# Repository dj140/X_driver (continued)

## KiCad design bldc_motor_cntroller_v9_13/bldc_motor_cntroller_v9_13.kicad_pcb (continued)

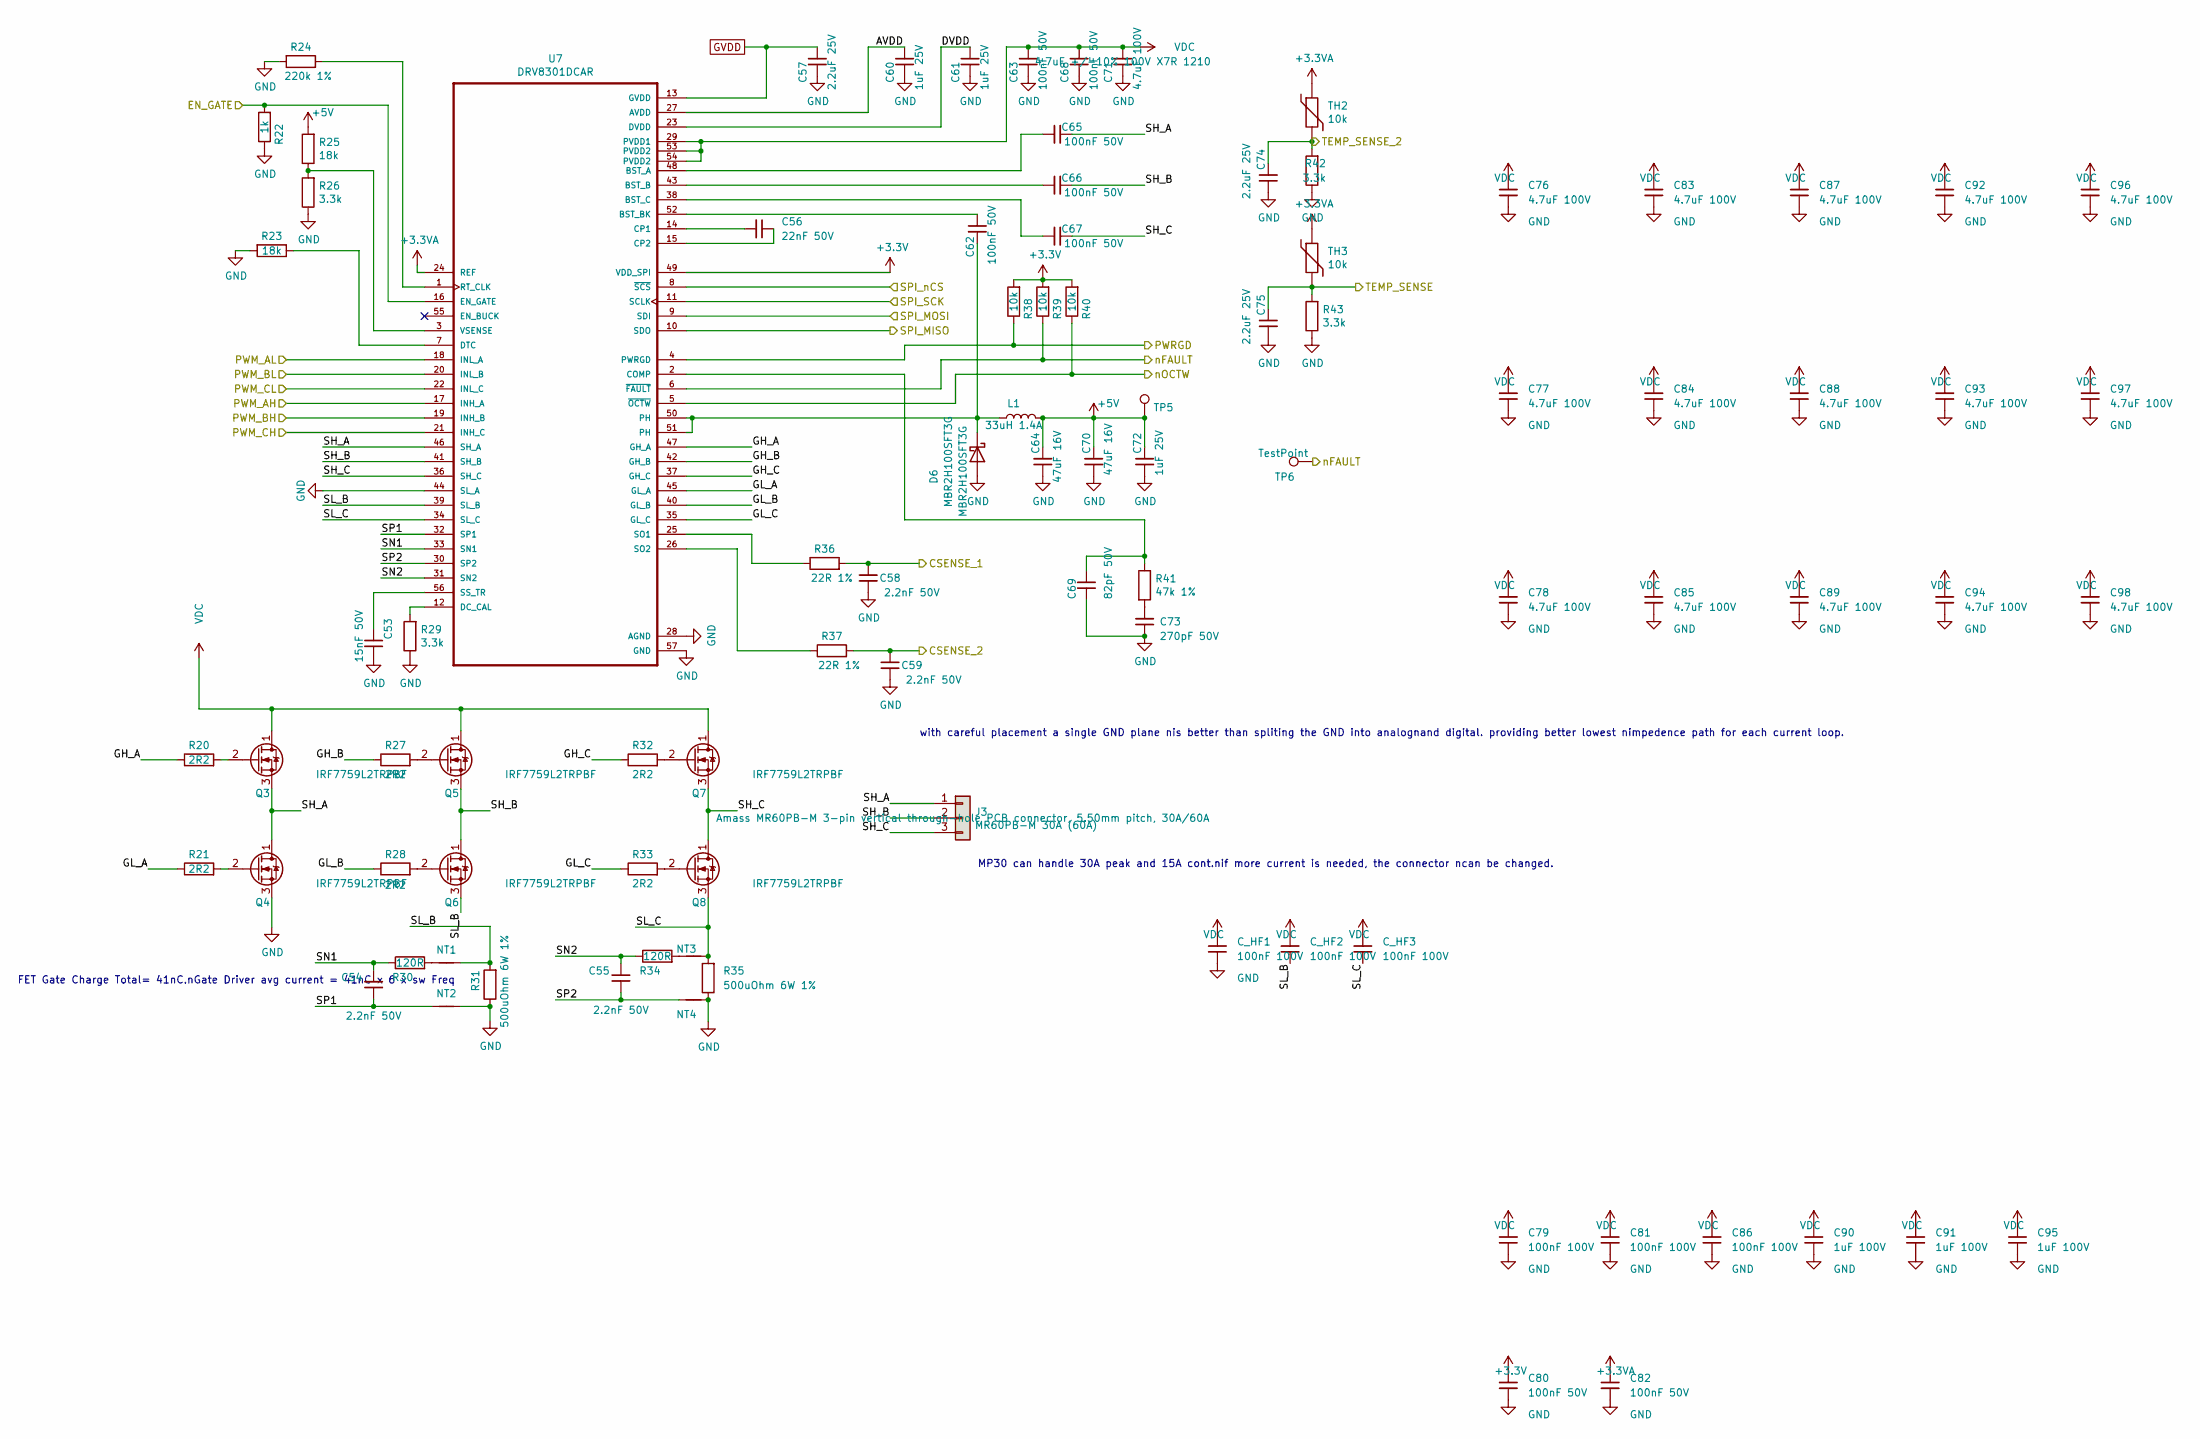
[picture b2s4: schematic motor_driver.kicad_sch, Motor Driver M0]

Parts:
C53: 15nF 50V; C_0402_1005Metric; MPN GCM155R71E153JA55D
C54, C55, C58, C59: 2.2nF 50V; C_0402_1005Metric; MPN C0402C222J3GEC7411; LCSC Part # C1531
C56: 22nF 50V; C_0402_1005Metric; MPN C0402C223K5REC7411; LCSC Part # C1532
C57, C74, C75: 2.2uF 25V; C_0402_1005Metric; MPN GRM155C81E225KE11D; LCSC Part # C12530
C60, C61, C72: 1uF 25V; C_0402_1005Metric; MPN GMK105CC6105MV-F; LCSC Part # C52923
C62, C65, C66, C67: 100nF 50V; C_0402_1005Metric; MPN GCM155L8EH104KE07D
C63, C68: 100nF 50V; C_0402_1005Metric; MPN GRM155R62A104KE14D
C64, C70: 47uF 16V; C_1206_3216Metric; MPN GRM32EC81C476KE15L; LCSC Part # C96123
C69: 82pF 50V; C_0402_1005Metric; MPN VJ0402A820JXACW1BC
C71: 4.7uF 100V; C_1210_3225Metric; MPN GRM32ER72A475KE14L; LCSC Part # C89632
C73: 270pF 50V; C_0402_1005Metric; MPN GRM1555C1H271FA01D
C76, C77, C78, C83, C84, C85, C87, C88, C89, C92, C93, C94, C96, C97, C98: 4.7uF 100V; C_1210_3225Metric; MPN GRM32ER72A475KE14L; LCSC C162515
C79, C81, C86: 100nF 100V; C_0603_1608Metric; MPN GCM188R72A104KA64D; LCSC C15725
C80, C82: 100nF 50V; C_0402_1005Metric; MPN CC0402KRX7R9BB104; LCSC C131394
C90, C91, C95: 1uF 100V; C_0805_2012Metric; MPN 0805B105K101NT; LCSC C396883
C_HF1, C_HF2, C_HF3: 100nF 100V; C_0603_1608Metric; MPN GCM188R72A104KA64D
D6: MBR2H100SFT3G; D_SOD-123F; MPN MBR2H100SFT3G
J3: MR60PB-M 30A (60A); AMASS_MR60PB-M_1x03_P5.50mm_Vertical; MPN MR60PB-M
L1: 33uH 1.4A; L_Taiyo-Yuden_NR-60xx; MPN NR6045T330M
NT1, NT2, NT3, NT4: Net-Tie_2; NetTie-2_SMD_Pad0.5mm
Q3, Q4, Q5, Q6, Q7, Q8: IRF7759L2TRPBF; DirectFET_L8; MPN IRF7759L2TRPBF; LCSC C520641
R20, R21, R27, R28, R32, R33: 2R2; R_0402_1005Metric; MPN CRCW04022R20FKEDC
R22: 1k; R_0402_1005Metric; MPN ERJ-2RKF1001X; LCSC Part # C11702
R23, R25: 18k; R_0402_1005Metric; MPN CRCW040218K0FKED; LCSC Part # C25762
R24: 220k 1%; R_0402_1005Metric; MPN CRCW0402220KFKEDC; LCSC Part # C25767
R26, R29, R42, R43: 3.3k; R_0402_1005Metric; MPN CRCW04023K30FKEDC; LCSC Part # C25890
R30, R34: 120R; R_0402_1005Metric; MPN ERJ-2RKF1200X; LCSC Part # C25079
R31, R35: 500uOhm 6W 1%; R_2512_6332Metric; MPN CSS2H-2512R-L500F
R36, R37: 22R 1%; R_0402_1005Metric; MPN CRCW040222R0FKEDC; LCSC Part # C25092
R38, R39, R40: 10k; R_0402_1005Metric; MPN CRCW040210K0FKEDC; LCSC Part # C25744
R41: 47k 1%; R_0402_1005Metric; MPN CRGP0402F47K; LCSC Part # C25792
TH2, TH3: 10k; R_0402_1005Metric; MPN CRCW040210K0FKEDC
TP5, TP6: TestPoint; TestPoint_Pad_D1.0mm
U7: DRV8301DCAR; DRV8301DCA_v9; MPN DRV8301DCAR

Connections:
+3.3V: C80.1, R38.2, R39.2, R40.2, U7.49 (VDD_SPI); also elsewhere on the board
+3.3VA: C82.1, TH2.1, TH3.1, U7.24 (REF); also elsewhere on the board
+5V: C64.1, C70.1, C72.1, L1.2, R25.2, TP5.1; also elsewhere on the board
/Microcontroller Interface/EN_GATE: R22.2, U7.16 (EN_GATE); also elsewhere on the board
/Microcontroller Interface/M0_AH: U7.17 (INH_A); also elsewhere on the board
/Microcontroller Interface/M0_AL: U7.18 (INL_A); also elsewhere on the board
/Microcontroller Interface/M0_BH: U7.19 (INH_B); also elsewhere on the board
/Microcontroller Interface/M0_BL: U7.20 (INL_B); also elsewhere on the board
/Microcontroller Interface/M0_CH: U7.21 (INH_C); also elsewhere on the board
/Microcontroller Interface/M0_CL: U7.22 (INL_C); also elsewhere on the board
/Microcontroller Interface/M0_SO1: C58.2, R36.2; also elsewhere on the board
/Microcontroller Interface/M0_SO2: C59.2, R37.2; also elsewhere on the board
/Microcontroller Interface/M0_TEMP: C75.1, R43.2, TH3.2; also elsewhere on the board
/Microcontroller Interface/SPI_M0_nCS: U7.8 (~SCS); also elsewhere on the board
/Microcontroller Interface/SPI_MISO: U7.10 (SDO); also elsewhere on the board
/Microcontroller Interface/SPI_MOSI: U7.9 (SDI); also elsewhere on the board
/Microcontroller Interface/SPI_SCK: U7.11 (SCLK); also elsewhere on the board
/Microcontroller Interface/nFAULT: R39.1, TP6.1, U7.6 (~FAULT); also elsewhere on the board
/Motor Driver/AVDD: C60.1, U7.27 (AVDD)
/Motor Driver/DVDD: C61.1, U7.23 (DVDD)
/Motor Driver/GH_A: R20.1, U7.47 (GH_A)
/Motor Driver/GH_B: R27.1, U7.42 (GH_B)
/Motor Driver/GH_C: R32.1, U7.37 (GH_C)
/Motor Driver/GL_A: R21.1, U7.45 (GL_A)
/Motor Driver/GL_B: R28.1, U7.40 (GL_B)
/Motor Driver/GL_C: R33.1, U7.35 (GL_C)
/Motor Driver/PWRGD: R38.1, U7.4 (PWRGD)
/Motor Driver/SH_A: C65.1, J3.1, Q3.3 (S), Q4.1 (D), U7.46 (SH_A)
/Motor Driver/SH_B: C66.1, J3.2, Q5.3 (S), Q6.1 (D), U7.41 (SH_B)
/Motor Driver/SH_C: C67.1, J3.3, Q7.3 (S), Q8.1 (D), U7.36 (SH_C)
/Motor Driver/SL_B: C_HF2.2, NT1.2, Q6.3 (S), R31.2, U7.39 (SL_B)
/Motor Driver/SL_C: C_HF3.2, NT3.2, Q8.3 (S), R35.2, U7.34 (SL_C)
/Motor Driver/SN1: C54.2, R30.1, U7.33 (SN1)
/Motor Driver/SN2: C55.2, R34.1, U7.31 (SN2)
/Motor Driver/SP1: C54.1, NT2.1, U7.32 (SP1)
/Motor Driver/SP2: C55.1, NT4.1, U7.30 (SP2)
/Motor Driver/TEMP_SENSE_2: C74.1, R42.2, TH2.2
/Motor Driver/nOCTW: R40.1, U7.5 (~OCTW)
GND: C53.1, C57.2, C58.1, C59.1, C60.2, C61.2, C63.2, C64.2, C68.2, C69.2, C70.2, C71.2, C72.2, C73.2, C74.2, C75.2, C76.2, C77.2, C78.2, C79.2, C80.2, C81.2, C82.2, C83.2, C84.2, C85.2, C86.2, C87.2, C88.2, C89.2, C90.2, C91.2, C92.2, C93.2, C94.2, C95.2, C96.2, C97.2, C98.2, C_HF1.2, D6.2 (A), NT2.2, NT4.2, Q4.3 (S), R22.1, R23.2, R24.2, R26.1, R29.1, R31.1, R35.1, R42.1, R43.1, U7.28 (AGND), U7.44 (SL_A), U7.57 (GND); also elsewhere on the board
GVDD: C57.1, U7.13 (GVDD); also elsewhere on the board
unnamed: C73.1, R41.2
unnamed: C62.1, D6.1 (K), L1.1, U7.50 (PH), U7.51 (PH)
unnamed: NT1.1, R30.2
unnamed: NT3.1, R34.2
unnamed: Q3.2 (G), R20.2
unnamed: Q4.2 (G), R21.2
unnamed: Q5.2 (G), R27.2
unnamed: Q6.2 (G), R28.2
unnamed: Q7.2 (G), R32.2
unnamed: Q8.2 (G), R33.2
unnamed: C65.2, U7.48 (BST_A)
unnamed: C66.2, U7.43 (BST_B)
unnamed: C62.2, U7.52 (BST_BK)
unnamed: C67.2, U7.38 (BST_C)
unnamed: C69.1, R41.1, U7.2 (COMP)
unnamed: C56.1, U7.14 (CP1)
unnamed: C56.2, U7.15 (CP2)
unnamed: R29.2, U7.12 (DC_CAL)
unnamed: R23.1, U7.7 (DTC)
unnamed: R24.1, U7.1 (RT_CLK)
unnamed: R36.1, U7.25 (SO1)
unnamed: R37.1, U7.26 (SO2)
unnamed: C53.2, U7.56 (SS_TR)
unnamed: R25.1, R26.2, U7.3 (VSENSE)
VDC: C63.1, C68.1, C71.1, C76.1, C77.1, C78.1, C79.1, C81.1, C83.1, C84.1, C85.1, C86.1, C87.1, C88.1, C89.1, C90.1, C91.1, C92.1, C93.1, C94.1, C95.1, C96.1, C97.1, C98.1, C_HF1.1, C_HF2.1, C_HF3.1, Q3.1 (D), Q5.1 (D), Q7.1 (D), U7.29 (PVDD1), U7.53 (PVDD2), U7.54 (PVDD2); also elsewhere on the board

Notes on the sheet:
MP30 can handle 30A peak and 15A cont.nif more current is needed, the connector ncan be changed.
FET Gate Charge Total= 41nC.nGate Driver avg current = 41nC x 6 x sw Freq
with careful placement a single GND plane nis better than spliting the GND into analognand digital. providing better lowest nimpedence path for each current loop.

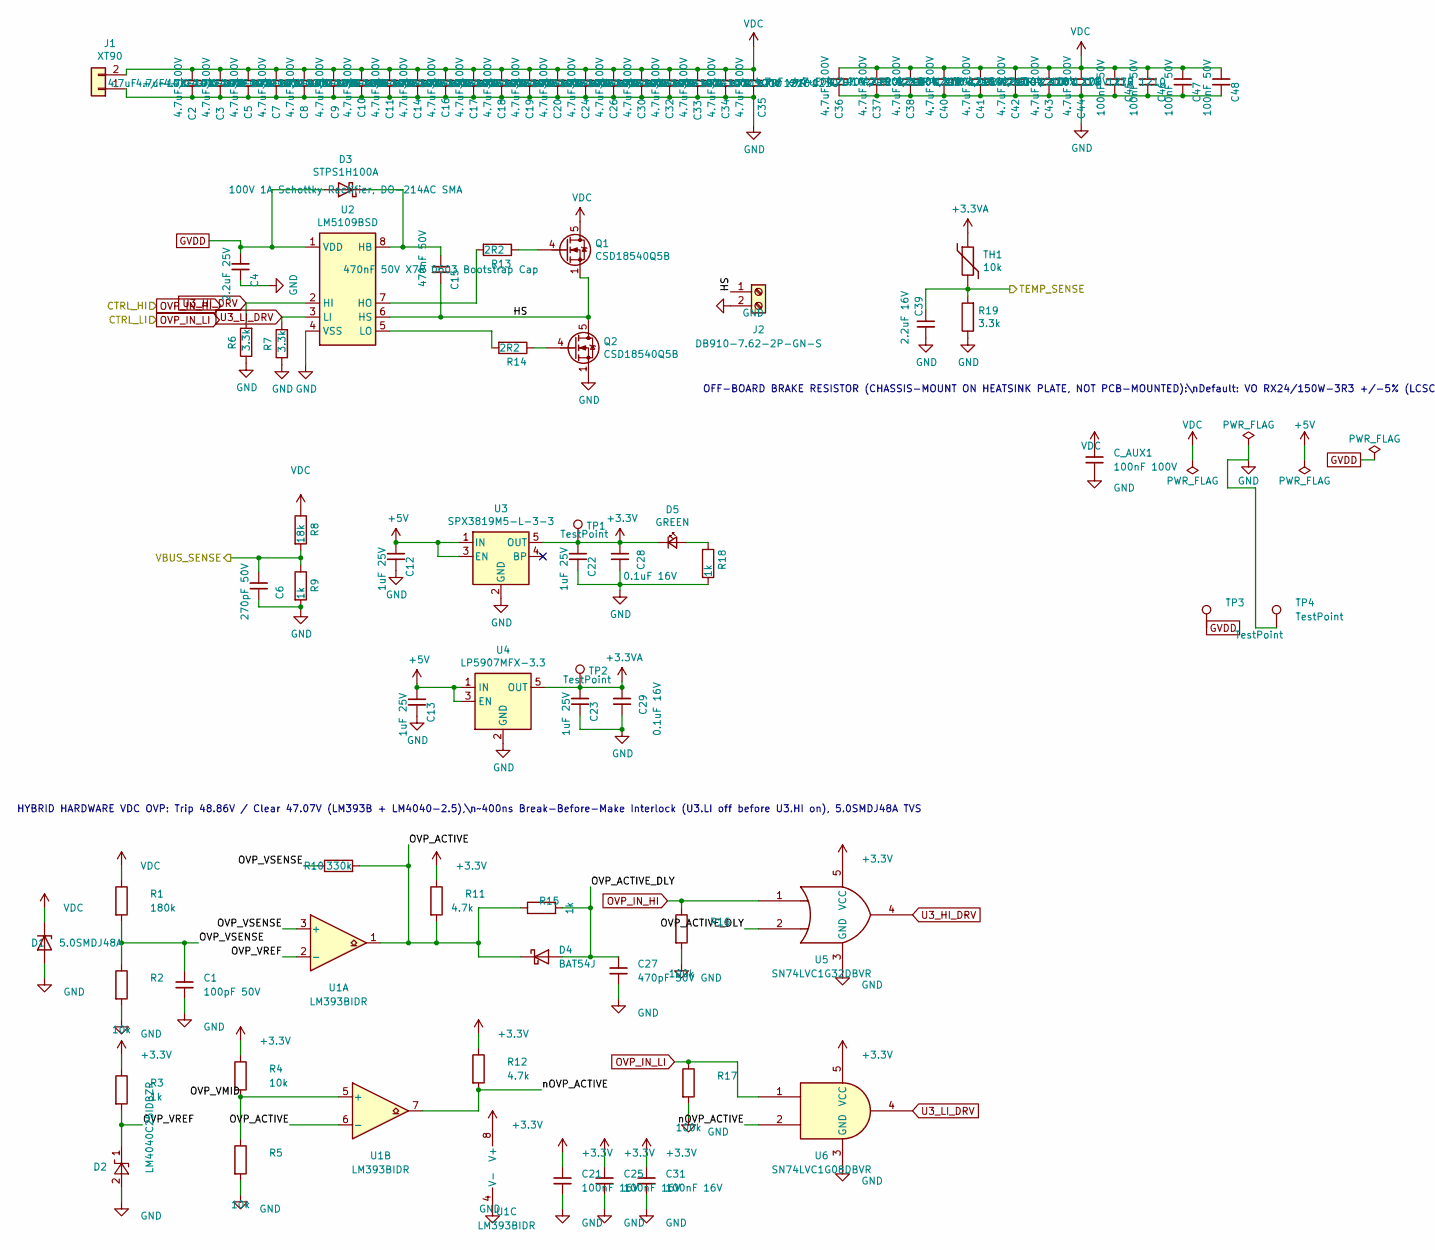
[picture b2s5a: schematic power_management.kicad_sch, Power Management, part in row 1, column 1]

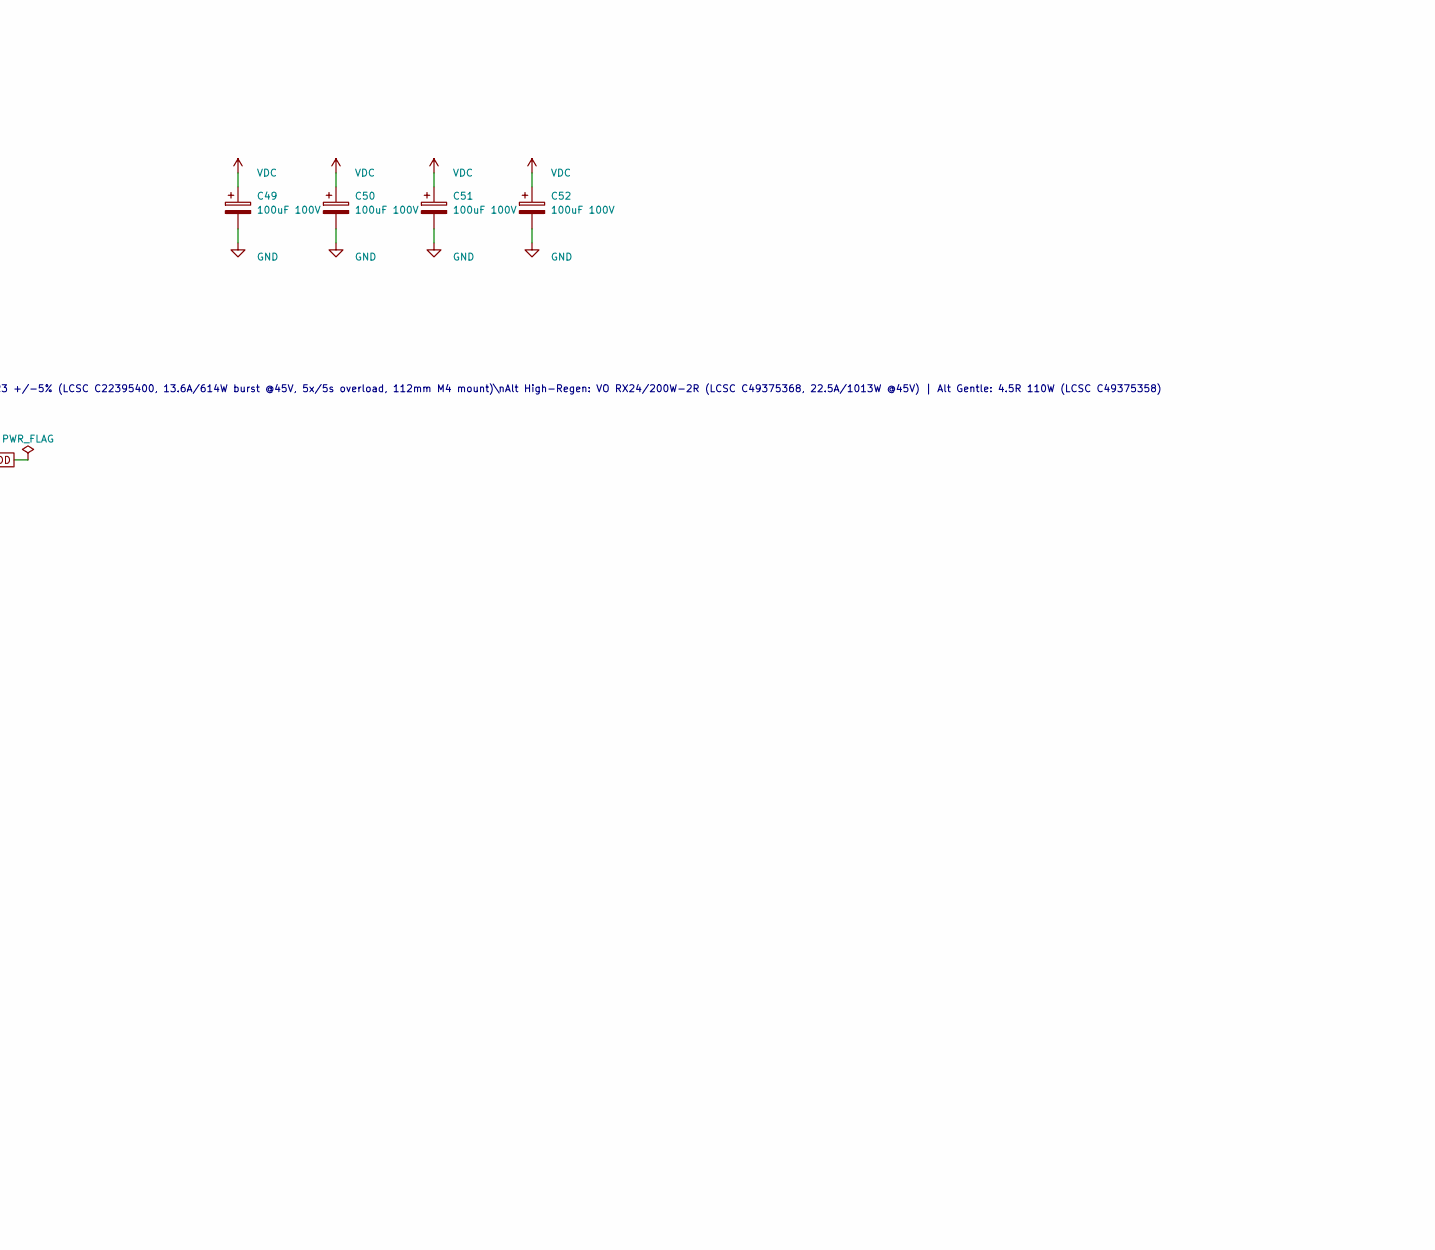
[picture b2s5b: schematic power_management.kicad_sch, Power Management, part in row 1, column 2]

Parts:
C1: 100pF 50V; C_0402_1005Metric; MPN GRM1555C1H101JA01D
C2, C3, C5, C7, C8, C9, C10, C11, C14, C16, C17, C18, C19, C20, C24, C26, C30, C32, C33, C34, C35, C36, C37, C38, C40, C41, C42, C43, C44: 4.7uF 100V; C_1210_3225Metric; MPN GRM32ER72A475KE14L; LCSC C162515
C4: 2.2uF 25V; C_0402_1005Metric; MPN GRM155R61E225ME15D; LCSC Part # C12530
C6: 270pF 50V; C_0402_1005Metric; MPN GRM1555C1H271FA01D
C12, C13, C22, C23: 1uF 25V; C_0402_1005Metric; MPN GMK105CC6105MV-F; LCSC Part # C52923
C15: 470nF 50V; C_0603_1608Metric; MPN GRM188R71H474KA93D; LCSC Part # C1525
C21, C25, C31: 100nF 16V; C_0402_1005Metric; MPN GRM155R62A104KE14D
C27: 470pF 50V; C_0402_1005Metric; MPN GRM1555C1H471JA01D
C28, C29: 0.1uF 16V; C_0402_1005Metric; MPN GRM155R62A104KE14D
C39: 2.2uF 16V; C_0402_1005Metric; MPN GRM155C81E225KE11D; LCSC Part # C12530
C45, C46, C47, C48: 100nF 50V; C_0402_1005Metric; MPN GCM155L8EH104KE07D
C49, C50, C51, C52: 100uF 100V; CP_Elec_10x10.5; MPN HV1K107M1010PZ; LCSC C42436546
C_AUX1: 100nF 100V; C_0603_1608Metric; MPN GCM188R72A104KA64D
D1: 5.0SMDJ48A; D_SMC; MPN 5.0SMDJ48A
D2: LM4040C25IDBZR; SOT-23; MPN LM4040C25IDBZR
D3: STPS1H100A; D_SMA; MPN STPS1H100A
D4: BAT54J; D_SOD-323F; MPN BAT54J,115
D5: GREEN; LED_0402_1005Metric
J1: XT90; AMASS_XT90-M_1x02_P10.90mm_Vertical; MPN XT90PB-M
J2: DB910-7.62-2P-GN-S; DORABO_DB910-7.62-2P; MPN DB910-7.62-2P-GN-S; LCSC C395876
Q1, Q2: CSD18540Q5B; TDSON-8-1
R1: 180k; R_0603_1608Metric; MPN RC0603FR-07180KL
R2, R4, R5: 10k; R_0402_1005Metric; MPN RC0402FR-0710KL
R3, R15: 1k; R_0402_1005Metric; MPN RC0402FR-071KL
R6, R7, R19: 3.3k; R_0402_1005Metric; MPN CRCW04023K30FKEDC; LCSC Part # C25890
R8: 18k; R_0402_1005Metric; MPN CRCW040218K0FKEDC; LCSC Part # C25762
R9, R18: 1k; R_0402_1005Metric; MPN ERJ-2RKF1001X; LCSC Part # C11702
R10: 330k; R_0402_1005Metric; MPN RC0402FR-07330KL
R11, R12: 4.7k; R_0402_1005Metric; MPN RC0402FR-074K7L
R13, R14: 2R2; R_0402_1005Metric; MPN CRCW04022R20FKEDC
R16, R17: 100k; R_0402_1005Metric; MPN RC0402FR-07100KL
TH1: 10k; R_0402_1005Metric; MPN CRCW040210K0FKEDC
TP1, TP2, TP3, TP4: TestPoint; TestPoint_Pad_D1.0mm
U1: LM393BIDR; SOIC-8_3.9x4.9mm_P1.27mm; MPN LM393BIDR
U2: LM5109BSD; WSON-8_4x4mm_P0.8mm
U3: SPX3819M5-L-3-3; SOT-23-5
U4: LP5907MFX-3.3; SOT-23-5
U5: SN74LVC1G32DBVR; SOT-23-5; MPN SN74LVC1G32DBVR
U6: SN74LVC1G08DBVR; SOT-23-5; MPN SN74LVC1G08DBVR

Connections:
+3.3V: C21.1, C22.1, C25.1, C28.1, C31.1, D5.1 (K), R3.1, R4.1, R11.1, R12.1, TP1.1, U1.8 (V+), U3.5 (OUT), U5.5 (VCC), U6.5 (VCC); also elsewhere on the board
+3.3VA: C23.1, C29.1, TH1.1, TP2.1, U4.5 (OUT); also elsewhere on the board
+5V: C12.1, C13.1, U3.1 (IN), U3.3 (EN), U4.1 (IN), U4.3 (EN); also elsewhere on the board
/Microcontroller Interface/AUX_TEMP: C39.1, R19.2, TH1.2; also elsewhere on the board
/Microcontroller Interface/VBUS_S: C6.1, R8.2, R9.1; also elsewhere on the board
/Power Management/HS: C15.2, J2.1, Q1.1 (S), Q1.2 (S), Q1.3 (S), Q2.5 (D), U2.6 (HS)
/Power Management/OVP_ACTIVE: D4.1 (K), R10.2, R11.2, R15.1, U1.1, U1.6 (-)
/Power Management/OVP_ACTIVE_DLY: C27.1, D4.2 (A), R15.2, U5.2
/Power Management/OVP_VMID: R4.2, R5.1, U1.5 (+)
/Power Management/OVP_VREF: D2.1 (K), R3.2, U1.2 (-)
/Power Management/OVP_VSENSE: C1.1, R1.2, R2.1, R10.1, U1.3 (+)
/Power Management/nOVP_ACTIVE: R12.2, U1.7, U6.2
GND: C1.2, C2.2, C3.2, C4.2, C5.2, C6.2, C7.2, C8.2, C9.2, C10.2, C11.2, C12.2, C13.2, C14.2, C16.2, C17.2, C18.2, C19.2, C20.2, C21.2, C22.2, C23.2, C24.2, C25.2, C26.2, C27.2, C28.2, C29.2, C30.2, C31.2, C32.2, C33.2, C34.2, C35.2, C36.2, C37.2, C38.2, C39.2, C40.2, C41.2, C42.2, C43.2, C44.2, C45.2, C46.2, C47.2, C48.2, C49.2, C50.2, C51.2, C52.2, C_AUX1.2, D1.2 (A), D2.2 (A), J1.1, J2.2, Q2.1 (S), Q2.2 (S), Q2.3 (S), R2.2, R5.2, R6.1, R7.1, R9.2, R16.2, R17.2, R18.2, R19.1, TP4.1, U1.4 (V-), U2.4 (VSS), U2.9 (VSS), U3.2 (GND), U4.2 (GND), U5.3 (GND), U6.3 (GND); also elsewhere on the board
GVDD: C4.1, D3.2 (A), TP3.1, U2.1 (VDD); also elsewhere on the board
unnamed: C15.1, D3.1 (K), U2.8 (HB)
unnamed: D5.2 (A), R18.1
unnamed: Q1.4 (G), R13.1
unnamed: Q2.4 (G), R14.1
unnamed: R13.2, U2.7 (HO)
unnamed: R14.2, U2.5 (LO)
OVP_IN_HI: R16.1, U5.1; also elsewhere on the board
OVP_IN_LI: R17.1, U6.1; also elsewhere on the board
U3_HI_DRV: R6.2, U2.2 (HI), U5.4
U3_LI_DRV: R7.2, U2.3 (LI), U6.4
VDC: C2.1, C3.1, C5.1, C7.1, C8.1, C9.1, C10.1, C11.1, C14.1, C16.1, C17.1, C18.1, C19.1, C20.1, C24.1, C26.1, C30.1, C32.1, C33.1, C34.1, C35.1, C36.1, C37.1, C38.1, C40.1, C41.1, C42.1, C43.1, C44.1, C45.1, C46.1, C47.1, C48.1, C49.1, C50.1, C51.1, C52.1, C_AUX1.1, D1.1 (K), J1.2, Q1.5 (D), R1.1, R8.1; also elsewhere on the board

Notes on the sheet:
OFF-BOARD BRAKE RESISTOR (CHASSIS-MOUNT ON HEATSINK PLATE, NOT PCB-MOUNTED):\nDefault: VO RX24/150W-3R3 +/-5% (LCSC C22395400, 13.6A/614W burst @45V, 5x/5s overload, 112mm M4 mount)\nAlt High-Regen: VO RX24/200W-2R (LCSC C49375368, 22.5A/1013W @45V) | Alt Gentle: 4.5R 110W (LCSC C49375358)
HYBRID HARDWARE VDC OVP: Trip 48.86V / Clear 47.07V (LM393B + LM4040-2.5),\n~400ns Break-Before-Make Interlock (U3.LI off before U3.HI on), 5.0SMDJ48A TVS

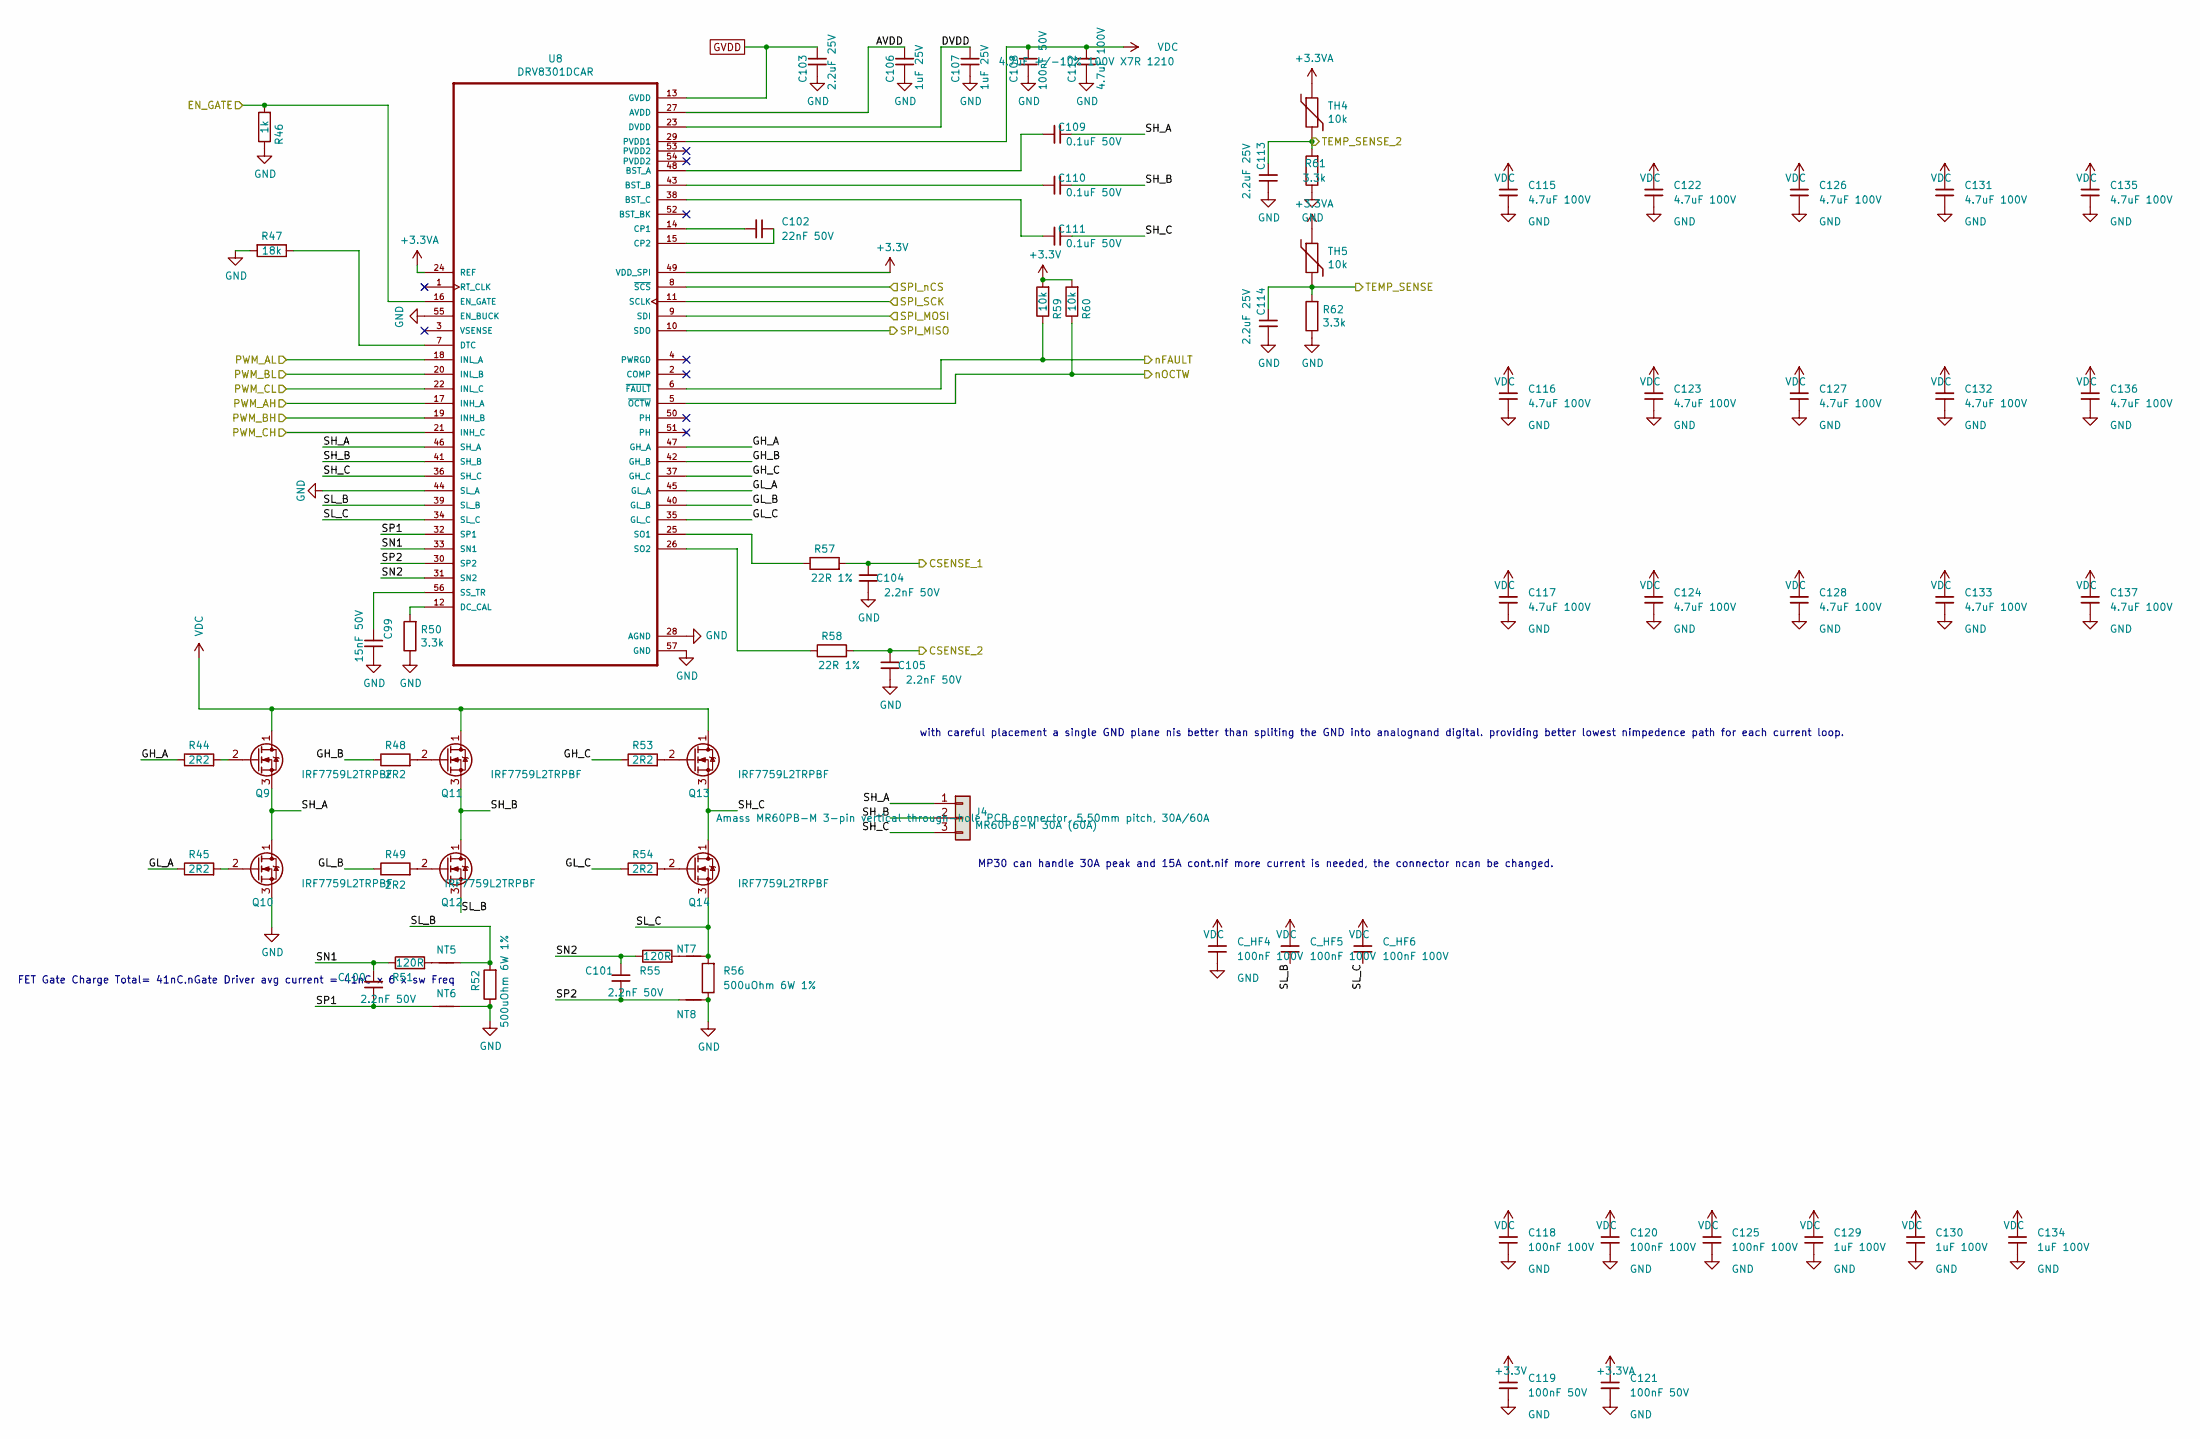
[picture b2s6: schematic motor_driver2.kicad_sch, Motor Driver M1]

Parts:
C99: 15nF 50V; C_0402_1005Metric; MPN GCM155R71E153JA55D
C100, C101, C104, C105: 2.2nF 50V; C_0402_1005Metric; MPN C0402C222J3GEC7411; LCSC Part # C1531
C102: 22nF 50V; C_0402_1005Metric; MPN C0402C223K5REC7411; LCSC Part # C1532
C103, C113, C114: 2.2uF 25V; C_0402_1005Metric; MPN GRM155C81E225KE11D; LCSC Part # C12530
C106, C107: 1uF 25V; C_0402_1005Metric; MPN GMK105CC6105MV-F; LCSC Part # C52923
C108: 100nF 50V; C_0402_1005Metric; MPN GRM155R62A104KE14D
C109, C110, C111: 0.1uF 50V; C_0402_1005Metric; MPN GCM155L8EH104KE07D
C112: 4.7uF 100V; C_1210_3225Metric; MPN GRM32ER72A475KE14L; LCSC Part # C89632
C115, C116, C117, C122, C123, C124, C126, C127, C128, C131, C132, C133, C135, C136, C137: 4.7uF 100V; C_1210_3225Metric; MPN GRM32ER72A475KE14L; LCSC C162515
C118, C120, C125: 100nF 100V; C_0603_1608Metric; MPN GCM188R72A104KA64D; LCSC C15725
C119, C121: 100nF 50V; C_0402_1005Metric; MPN CC0402KRX7R9BB104; LCSC C131394
C129, C130, C134: 1uF 100V; C_0805_2012Metric; MPN 0805B105K101NT; LCSC C396883
C_HF4, C_HF5, C_HF6: 100nF 100V; C_0603_1608Metric; MPN GCM188R72A104KA64D
J4: MR60PB-M 30A (60A); AMASS_MR60PB-M_1x03_P5.50mm_Vertical; MPN MR60PB-M
NT5, NT6, NT7, NT8: Net-Tie_2; NetTie-2_SMD_Pad0.5mm
Q9, Q10, Q11, Q12, Q13, Q14: IRF7759L2TRPBF; DirectFET_L8; MPN IRF7759L2TRPBF; LCSC C520641
R44, R45, R48, R49, R53, R54: 2R2; R_0402_1005Metric; MPN CRCW04022R20FKEDC
R46: 1k; R_0402_1005Metric; MPN ERJ-2RKF1001X; LCSC Part # C11702
R47: 18k; R_0402_1005Metric; MPN CRCW040218K0FKED; LCSC Part # C25762
R50, R61, R62: 3.3k; R_0402_1005Metric; MPN CRCW04023K30FKEDC; LCSC Part # C25890
R51, R55: 120R; R_0402_1005Metric; MPN ERJ-2RKF1200X; LCSC Part # C25079
R52, R56: 500uOhm 6W 1%; R_2512_6332Metric; MPN CSS2H-2512R-L500F
R57, R58: 22R 1%; R_0402_1005Metric; MPN CRCW040222R0FKEDC; LCSC Part # C25092
R59, R60: 10k; R_0402_1005Metric; MPN CRCW040210K0FKEDC; LCSC Part # C25744
TH4, TH5: 10k; R_0402_1005Metric; MPN CRCW040210K0FKEDC
U8: DRV8301DCAR; DRV8301DCA_v9; MPN DRV8301DCAR

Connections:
+3.3V: C119.1, R59.2, R60.2, U8.49 (VDD_SPI); also elsewhere on the board
+3.3VA: C121.1, TH4.1, TH5.1, U8.24 (REF); also elsewhere on the board
/Microcontroller Interface/EN_GATE: R46.2, U8.16 (EN_GATE); also elsewhere on the board
/Microcontroller Interface/M1_AH: U8.17 (INH_A); also elsewhere on the board
/Microcontroller Interface/M1_AL: U8.18 (INL_A); also elsewhere on the board
/Microcontroller Interface/M1_BH: U8.19 (INH_B); also elsewhere on the board
/Microcontroller Interface/M1_BL: U8.20 (INL_B); also elsewhere on the board
/Microcontroller Interface/M1_CH: U8.21 (INH_C); also elsewhere on the board
/Microcontroller Interface/M1_CL: U8.22 (INL_C); also elsewhere on the board
/Microcontroller Interface/M1_SO1: C104.2, R57.2; also elsewhere on the board
/Microcontroller Interface/M1_SO2: C105.2, R58.2; also elsewhere on the board
/Microcontroller Interface/M1_TEMP: C114.1, R62.2, TH5.2; also elsewhere on the board
/Microcontroller Interface/SPI_M1_nCS: U8.8 (~SCS); also elsewhere on the board
/Microcontroller Interface/SPI_MISO: U8.10 (SDO); also elsewhere on the board
/Microcontroller Interface/SPI_MOSI: U8.9 (SDI); also elsewhere on the board
/Microcontroller Interface/SPI_SCK: U8.11 (SCLK); also elsewhere on the board
/Microcontroller Interface/nFAULT: R59.1, U8.6 (~FAULT); also elsewhere on the board
/Motor_Driver2/AVDD: C106.1, U8.27 (AVDD)
/Motor_Driver2/DVDD: C107.1, U8.23 (DVDD)
/Motor_Driver2/GH_A: R44.1, U8.47 (GH_A)
/Motor_Driver2/GH_B: R48.1, U8.42 (GH_B)
/Motor_Driver2/GH_C: R53.1, U8.37 (GH_C)
/Motor_Driver2/GL_A: R45.1, U8.45 (GL_A)
/Motor_Driver2/GL_B: R49.1, U8.40 (GL_B)
/Motor_Driver2/GL_C: R54.1, U8.35 (GL_C)
/Motor_Driver2/SH_A: C109.1, J4.1, Q9.3 (S), Q10.1 (D), U8.46 (SH_A)
/Motor_Driver2/SH_B: C110.1, J4.2, Q11.3 (S), Q12.1 (D), U8.41 (SH_B)
/Motor_Driver2/SH_C: C111.1, J4.3, Q13.3 (S), Q14.1 (D), U8.36 (SH_C)
/Motor_Driver2/SL_B: C_HF5.2, NT5.2, Q12.3 (S), R52.2, U8.39 (SL_B)
/Motor_Driver2/SL_C: C_HF6.2, NT7.2, Q14.3 (S), R56.2, U8.34 (SL_C)
/Motor_Driver2/SN1: C100.2, R51.1, U8.33 (SN1)
/Motor_Driver2/SN2: C101.2, R55.1, U8.31 (SN2)
/Motor_Driver2/SP1: C100.1, NT6.1, U8.32 (SP1)
/Motor_Driver2/SP2: C101.1, NT8.1, U8.30 (SP2)
/Motor_Driver2/TEMP_SENSE_2: C113.1, R61.2, TH4.2
/Motor_Driver2/nOCTW: R60.1, U8.5 (~OCTW)
GND: C99.1, C103.2, C104.1, C105.1, C106.2, C107.2, C108.2, C112.2, C113.2, C114.2, C115.2, C116.2, C117.2, C118.2, C119.2, C120.2, C121.2, C122.2, C123.2, C124.2, C125.2, C126.2, C127.2, C128.2, C129.2, C130.2, C131.2, C132.2, C133.2, C134.2, C135.2, C136.2, C137.2, C_HF4.2, NT6.2, NT8.2, Q10.3 (S), R46.1, R47.2, R50.1, R52.1, R56.1, R61.1, R62.1, U8.28 (AGND), U8.44 (SL_A), U8.55 (EN_BUCK), U8.57 (GND); also elsewhere on the board
GVDD: C103.1, U8.13 (GVDD); also elsewhere on the board
unnamed: NT5.1, R51.2
unnamed: NT7.1, R55.2
unnamed: Q9.2 (G), R44.2
unnamed: Q10.2 (G), R45.2
unnamed: Q11.2 (G), R48.2
unnamed: Q12.2 (G), R49.2
unnamed: Q13.2 (G), R53.2
unnamed: Q14.2 (G), R54.2
unnamed: C109.2, U8.48 (BST_A)
unnamed: C110.2, U8.43 (BST_B)
unnamed: C111.2, U8.38 (BST_C)
unnamed: C102.1, U8.14 (CP1)
unnamed: C102.2, U8.15 (CP2)
unnamed: R50.2, U8.12 (DC_CAL)
unnamed: R47.1, U8.7 (DTC)
unnamed: R57.1, U8.25 (SO1)
unnamed: R58.1, U8.26 (SO2)
unnamed: C99.2, U8.56 (SS_TR)
VDC: C108.1, C112.1, C115.1, C116.1, C117.1, C118.1, C120.1, C122.1, C123.1, C124.1, C125.1, C126.1, C127.1, C128.1, C129.1, C130.1, C131.1, C132.1, C133.1, C134.1, C135.1, C136.1, C137.1, C_HF4.1, C_HF5.1, C_HF6.1, Q9.1 (D), Q11.1 (D), Q13.1 (D), U8.29 (PVDD1); also elsewhere on the board

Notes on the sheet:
FET Gate Charge Total= 41nC.nGate Driver avg current = 41nC x 6 x sw Freq
MP30 can handle 30A peak and 15A cont.nif more current is needed, the connector ncan be changed.
with careful placement a single GND plane nis better than spliting the GND into analognand digital. providing better lowest nimpedence path for each current loop.

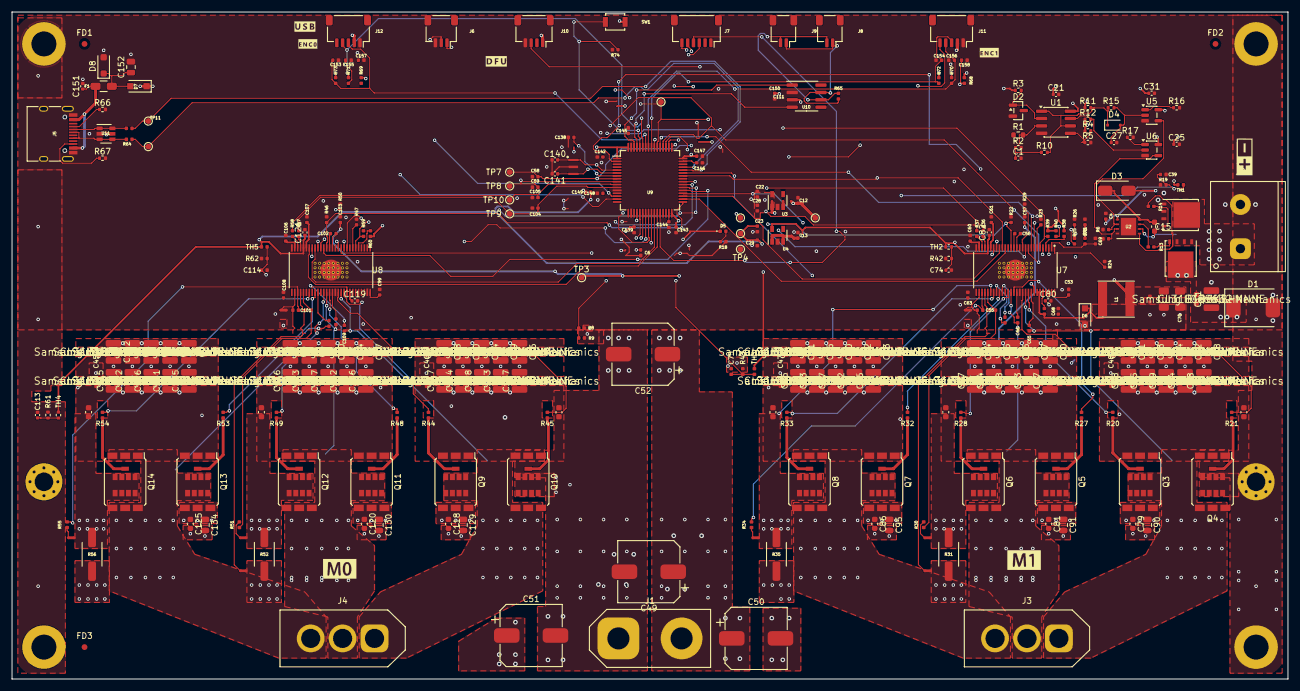
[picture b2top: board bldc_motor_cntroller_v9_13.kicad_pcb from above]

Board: 4 copper layers, 220.0 x 115.0 mm, 329 parts (0 on the bottom side), 165 nets.

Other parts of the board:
G1: LOGO; M00
G2: LOGO; M1
G3: LOGO; batt
G4: LOGO; DFU
G5: LOGO; USB
G6: LOGO; ENC0
G7: LOGO; ENC1

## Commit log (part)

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2021-05-30 Add files via upload
    first commit
